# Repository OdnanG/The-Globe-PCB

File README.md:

Projct name: The Globe
The Globe is a simple desk toy that provides local time using the "time" 
library of Python and has a small cool-looking globe spinning at a speed 
set by the user.
To use The Globe simply connect it to a power source and slide the switch
at the top ofthe box. This will turn on an LED light that will be picked 
up by a light sensor, subsequently turning on the clock and making the globe
spin. The angular velocity of the globe can be changed via a potentiometer
located in between the LCD clock display and the on-switch. If you have the
PocketBeagle hooked up to a computer and an IDE like Cloud9 open, you can see 
the servo duty being used and adjust the velocity based on that. Duty ranges 
from 15 to 80, making it coser to 80 will reduce velocity, while nearing it 
to 20 will increase velocity; once the duty cycle goes under 20, the globe
will begin spinning at full velocity in the opposite direction of how it usually
spins. If you only have the PocketBeagle connected to power rather than a computer,
you can still estimate how fast the globe will spin, simply remember that the
further left the potentiometer is turned, the faster the globe will spin, and
if it is turned all the way to the left, it will spin in the opposite direcion.

For a more detailed guide in how The Globe works and how it was built, check out
this Hackster.io page.

In this repository you will find everything needed to create a PCB of The Globe, enjoy.

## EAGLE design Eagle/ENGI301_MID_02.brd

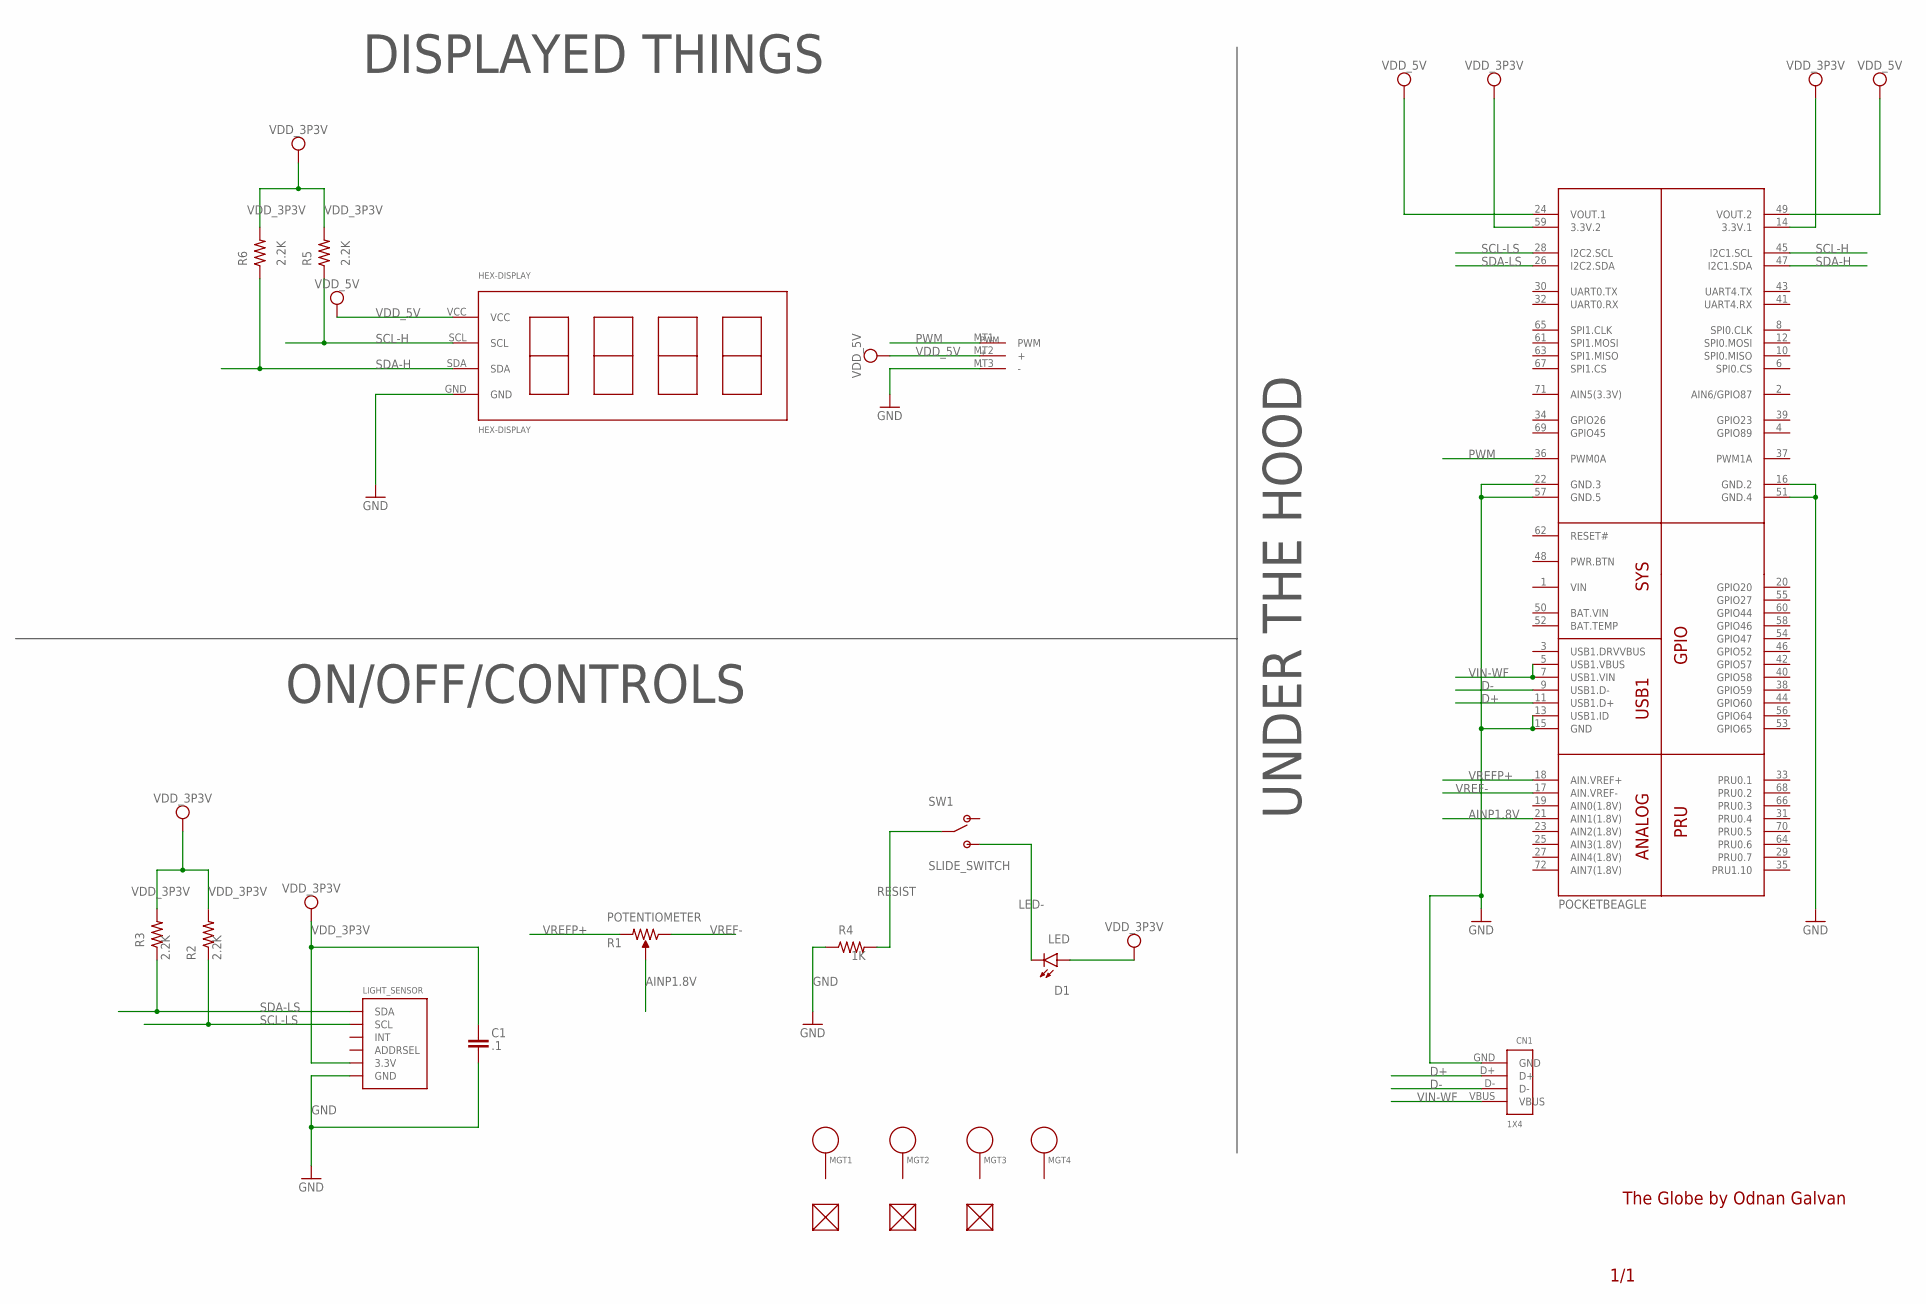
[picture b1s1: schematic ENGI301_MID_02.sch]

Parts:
C1: .1; C0603
CN1: 1X4; USBCONNECTOR
D1: LED; EIA-STD
FUD1, FUD2, FUD3: FIDUCIAL; FIDUCIAL_40MIL
LIGHT_SENSOR: TSL2561; TSL2561_FN
MGT1, MGT2, MGT3, MGT4: MOUNTING_HOLE
R1: POTENTIOMETER; POT-PO90S
R2, R3, R5, R6: 2.2K; R0603
R4: 1K; R0603
SW1: SLIDE_SWITCH; JS202011SCQN
U1: POCKETBEAGLE
U$1: HEX-DISPLAY
U$2: SERVO

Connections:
AINP1.8V: R1.S, U1.21 (AIN1(1.8V))
BAT.VIN: U1.50 (BAT.VIN)
D+: CN1.D+, U1.11 (USB1.D+)
D-: CN1.D-, U1.9 (USB1.D-)
GND: C1.2, CN1.GND, LIGHT_SENSOR.VSS (GND), R4.1, U1.13 (USB1.ID), U1.15 (GND), U1.16 (GND.2), U1.22 (GND.3), U1.51 (GND.4), U1.57 (GND.5), U$1.GND, U$2.MT3 (-)
LED-: D1.P$2 (C), SW1.3 (POS2), SW1.6 (POS2)
PWM: U1.36 (PWM0A), U$2.MT1 (PWM)
RESIST: R4.2, SW1.2 (COMM), SW1.5 (COMM)
SCL-H: R5.1, U1.45 (I2C1.SCL), U$1.SCL
SCL-LS: LIGHT_SENSOR.CLK (SCL), R2.1, U1.28 (I2C2.SCL)
SDA-H: R6.1, U1.47 (I2C1.SDA), U$1.SDA
SDA-LS: LIGHT_SENSOR.DATA (SDA), R3.1, U1.26 (I2C2.SDA)
VDD_3P3V: C1.1, D1.P$1 (A), LIGHT_SENSOR.VDD (3.3V), R2.2, R3.2, R5.2, R6.2, U1.14 (3.3V.1), U1.59 (3.3V.2)
VDD_5V: U1.24 (VOUT.1), U1.49 (VOUT.2), U$1.VCC, U$2.MT2 (+)
VIN: U1.1 (VIN)
VIN-WF: CN1.VBUS, U1.5 (USB1.VBUS), U1.7 (USB1.VIN)
VREF-: R1.CCW, U1.17 (AIN.VREF-)
VREFP+: R1.CW, U1.18 (AIN.VREF+)

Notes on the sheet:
The Globe by Odnan Galvan
1/1
ON/OFF/CONTROLS
UNDER THE HOOD
DISPLAYED THINGS

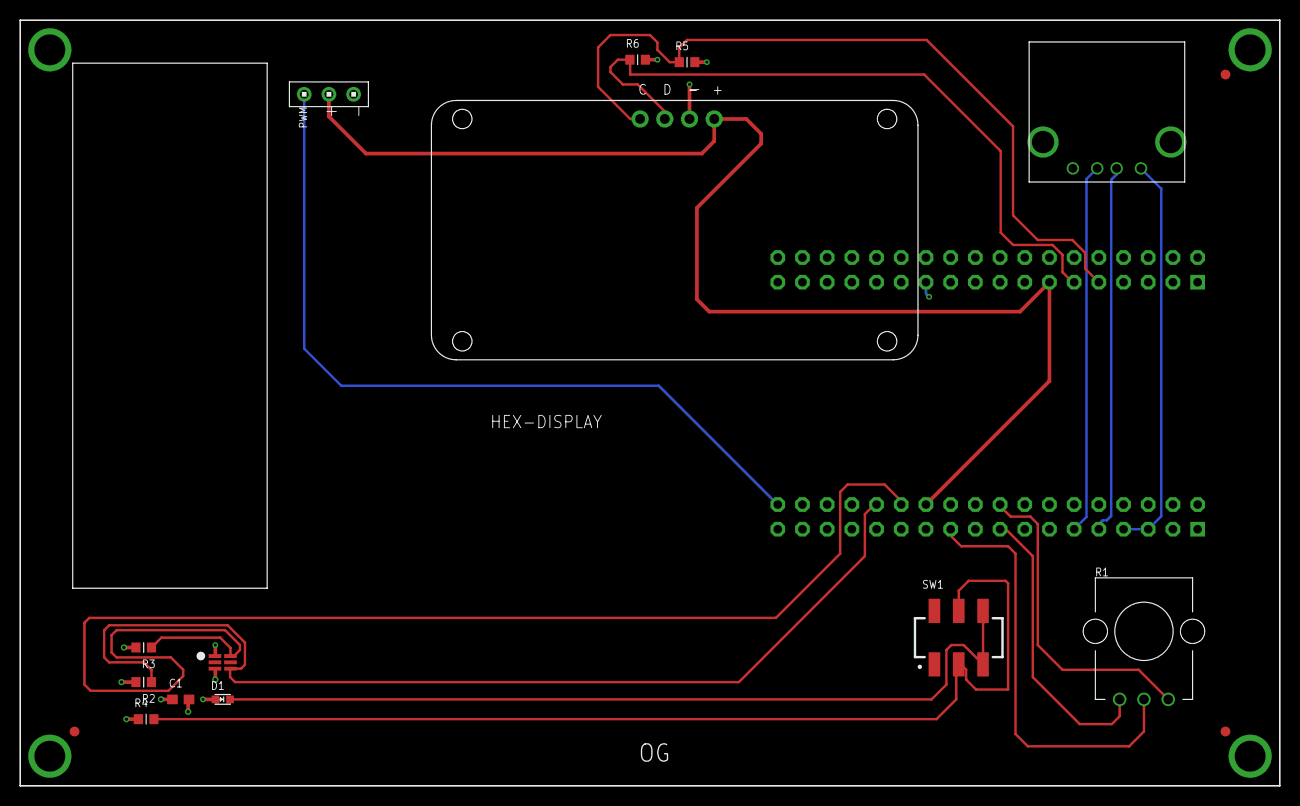
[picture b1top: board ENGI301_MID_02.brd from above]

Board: 4 copper layers, 129.5 x 78.7 mm, 21 parts (1 on the bottom side), 16 nets.

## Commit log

2019-12-18 Create k
2019-12-18 Create doc
2019-12-18 Create ok
